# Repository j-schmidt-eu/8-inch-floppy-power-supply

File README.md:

# 8-inch floppy drive - Power supply

> The 8" floppy drive power suplly can be used to power 8-inch floppy disk drives (using a suitable cable).

## Table of Contents
- [Introduction](#Introduction)
- [Specifications](#Specifications)
- [Setup](#Setup)
- [Compatibility](#Compatibility)
- [Cables](#Cables)
- [Manufacturing](#Manufacturing)
- [FAQ](#FAQ)
- [Licensing](#Licensing)

## Introduction
Many 8-inch floppy drives use different sockets and pinouts for power delivery. They also required power lines with up to 24V DC, some may need -5V DC lines and others even need a direct 120V/230V AC connection. This is a problem, since modern ATX power supplies only supply lines up to 12V.
To solve this problem a seperate power supply is necessary that provides all necessary power lines. Different connection cables can be used to power drives with different connectors.
This project aims to provide the schematic, PCB design and firmware source code to build such a supply.
The assembly consists of two part, a regular AC-DC 24V 100W power supply and an DC-DC conversion board that generates the auxillary voltages.

## Specifications

### Assembly Specifications
- Power
  - Input voltage: 120V/230V AC
  - Maximum input current: 1.0A@120V / 0.5A@230V
  - Input Connector: 3-pin screw terminal
  - Fusing: T 2.5A@120V / T 1.6A@230V

### Board Specifications
- Power
  - Input voltage: 24V DC
  - Maximum input current: 4.2A
  - Input Connector: 4-pin screw terminal
- Maximum number of drives per adapter: 2
- Pass-through voltages:
  - 24V DC 83W
- Output voltages:
  - +5V DC 15W
  - -5V DC 2W

## Setup
The power supply can drive up to two drives (using a Y/splitter cable) and an adapter board (via AUX power socket).

### Connections
Check to manual of the drive you'd like to power for the correct pinout of the power socket.

Some drives required a direct mains AC line connection. Make sure that your drive model is compatible with your mains AC voltage!

__**Important: Connecting the wrong mains AC voltage to your drive will destoy it!**__

You can search for the right AC and DC cable in the [list of drives](#Compatibility) and/or the [list of cables](#Cables) below.

### Fusing
The power input cable should have an inline fuse holder installed. The correct fuse has to be selected depending on the voltage of the mains AC line.

_**WARNING! RISK OF ELECTRIC SHOCK! Power cable must be unplugged prior to opening the fuse holder!**_

### Start-up
Begin with all power cables disconnected. Connect the drive and the power supply with the right DC cable. (If applicable) Connect the AC adaptor cable to the drive.
Now connect the power supply and (if applicable) the AC adaptor cable to mains using a power cable.

## Compatibility
The following list shows some 8-inch floppy drive models and the respective cables that should be correct for them.

| Model | DC cable | AC cable | Tested<sup>1</sup> |
| ----- | -------- | -------- | ------ |
| Mitsubishi M2896-63 | [TE Connectivity 1-480270-0](#TE-Connectivity-1-480270-0) | - | ❓ |
| NEC FD1165 | [TE Connectivity 171822-7](#TE-Connectivity-171822-7) | - | ❓ |
| Shugart SA800<br>Shugart SA801 | [TE Connectivity 1-480270-0](#TE-Connectivity-1-480270-0) | [TE Connectivity 1-480304-0](#TE-Connectivity-1-480304-0) | ❓ |
| Shugart SA810<br>Shugart SA860 | [TE Connectivity 1-480763-0](#TE-Connectivity-1-480763-0) | - | ❓ |
| Shugart SA850<br>Shugart SA851 | [TE Connectivity 1-480270-0](#TE-Connectivity-1-480270-0) | [TE Connectivity 1-480700-0](#TE-Connectivity-1-480700-0) | ❓ |
| Tandon TM848-1E<br>Tandon TM848-2E | [TE Connectivity 1-480270-0](#TE-Connectivity-1-480270-0) | - | ❓ |
| Y-E DATA YD-180 | [TE Connectivity 1-480270-0](#TE-Connectivity-1-480270-0) | - | ✅ |

<sup>1</sup> ✅: Cable(s) have been successfully tested. ❓: Cable(s) should be correct according to the manual, but haven't been tested yet.<br>

## Cables
The cable drawings were designed using [Microsoft Visio](https://en.wikipedia.org/wiki/Microsoft_Visio). The Visio files are located in the [Cables](Cables) sub-folders.

### DC cables
#### TE Connectivity 1-480270-0
[PDF](Cables/Floppy%20DC/TE%20Connectivity%201-480270-0.pdf)<br>
[Sample image](Cables/Floppy%20DC/TE%20Connectivity%201-480270-0.jpg)

#### TE Connectivity 1-480763-0
[PDF](Cables/Floppy%20DC/TE%20Connectivity%201-480763-0.pdf)<br>
[Sample image](Cables/Floppy%20DC/TE%20Connectivity%201-480763-0.jpg)

#### TE Connectivity 171822-7
[PDF](Cables/Floppy%20DC/TE%20Connectivity%20171822-7.pdf)<br>
[Sample image](Cables/Floppy%20DC/TE%20Connectivity%20171822-7.jpg)

#### Y-cable/splitter cable
[PDF](Cables/Floppy%20DC/Y-cable,%20splitter%20cable.pdf)<br>
[Sample image](Cables/Floppy%20DC/Y-cable,%20splitter%20cable.jpg)

### AC cables
#### TE Connectivity 1-480304-0
[PDF](Cables/Floppy%20AC/TE%20Connectivity%201-480304-0.pdf)<br>
[Sample image](Cables/Floppy%20AC/TE%20Connectivity%201-480304-0.jpg)

#### TE Connectivity 1-480700-0
[PDF](Cables/Floppy%20AC/TE%20Connectivity%201-480700-0.pdf)<br>
[Sample image](Cables/Floppy%20AC/TE%20Connectivity%201-480700-0.jpg)

### AUX cable
#### TE Connectivity 171822-4
[PDF](Cables/Aux%20DC/TE%20Connectivity%20171822-4.pdf)<br>
[Sample image](Cables/Aux%20DC/TE%20Connectivity%20171822-4.jpg)

## Manufacturing
The schematics and PCB were designed using [KiCad](https://kicad-pcb.org/). The KiCad project is located in the [Schematics & PCB](Schematics%20&%20PCB) folder. 

### Schematic
[PDF](Schematics%20&%20PCB/8%20Inch%20Floppy%20Power%20Supply/8%20Inch%20Floppy%20Power%20Supply.pdf)<br>
[PNG](Schematics%20&%20PCB/8%20Inch%20Floppy%20Power%20Supply/8%20Inch%20Floppy%20Power%20Supply.png)

### PCB Gerber files
[ZIP](Schematics%20&%20PCB/8%20Inch%20Floppy%20Power%20Supply/pcb.zip)

### PCB manufacturing
The board has a size of 51.5mm x 63mm, a minimum trace distance of 0.2mm and the minimal drill diameter is 0.8mm.
There are two layers and a total of 43 holes to drill. All holes, except for the two mounting holes, are plated.

If you are within the EU, you may want to consider choosing AISLER as your PCB manufacturer.

[PCB on AISLER](https://aisler.net/p/IWASNETN)

### Bill of materials
| Reference | Component | Housing /<br>Footprint | Type | Quantity |
| --------- | --------- | ---------------------- | ---- | -------- |
| C3 | Electrolytic Capacitor 2200 µF 35V | Radial D16.0mm P7.50mm | Yageo SY035M2200B7F-1632<sup>2</sup> | 1 |
| C5 | Electrolytic Capacitor 470µF 6.3V | Radial D8.0mm P3.50mm | Yageo SY006M0470B3F-0811<sup>2</sup> | 1 |
| C7 | Electrolytic Capacitor 220µF 6.3V | Radial D8.0mm P3.50mm | Yageo SY006M0220BZF-0611<sup>2</sup> | 1 |
| C4 | Ceramic Capacitor 1µF 50V | Disc D7.5mm W4.4mm P5.00mm | Kemet C330C105M5U5TA+<sup>2</sup>  | 1 |
| C6, C8 | Ceramic Capacitor 470nF 50V | Disc D5.1mm W3.2mm P5.00mm | Kemet C322C474M5U5TA+<sup>2</sup>  | 1 |
| J1 | AUX power out socket | 1 x 2 x 2.54mm | Molex 1053131202 | 1 |
| J2 | Power in screw terminal | 1 x 2 x 9.5mm | Degson DG950-9.5-02P-14-00AH | 2 |
| J3 | Main power out socket | 2 x 4 x 3.0mm | Molex 430450800 | 1 |
| U1 | 2W 5V isolated DC-DC Converter | TRACO TMR xx | Mean Well SPAN02B-05<sup>2</sup> | 1 |
| U2 | 15W 5V isolated DC-DC Converter | TRACO TEN10 xx | Mean Well SKA15B-05<sup>2</sup> | 1 |

<sup>2</sup> Suggestion; Other types may be used. <br>

## FAQ
##### My drive is not listed in the compatibility list, will it work?
>**Check the manual of your drive to see what kind of connector and pinout is used.
Go through the available cables to see if one matches the requirments of your drive. If that is the case, the drive will very likely work.**

## Licensing
This project is licensed under the [CC BY-NC-ND 4.0 license](LICENSE).

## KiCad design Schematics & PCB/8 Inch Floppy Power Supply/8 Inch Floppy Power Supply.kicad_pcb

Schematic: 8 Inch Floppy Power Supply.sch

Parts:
C3: 2200u; CP_Radial_D16.0mm_P7.50mm
C4: 1u; C_Disc_D7.5mm_W4.4mm_P5.00mm
C5: 470u; CP_Radial_D8.0mm_P3.50mm
C6, C8: 330n; C_Disc_D5.1mm_W3.2mm_P5.00mm
C7: 220u; CP_Radial_D8.0mm_P3.50mm
J1: AUX; Molex_NanoFit_1x02x2.50mm_Angled
J2: IN; Degson DG950-9.5-04P-1Y-00AH
J3: OUT; Molex_Microfit3_Header_02x04_Angled_43045-080x
U1: SPAN02B-05; Converter_DCDC_TRACO_TMR-xxxx_THT
U2: SKE10B-05; Converter_DCDC_TRACO_TEN10-xxxx_Single_THT

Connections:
+5V_DC: C5.1, C6.1, J1.2, J3.5, U2.3
+5V_GND: C5.2, C6.2, J1.1, J3.1, U2.5
+24V_DC: C3.1, C4.1, J2.1, J2.2, J3.8, U1.2, U2.1
+24V_GND: C3.2, C4.2, J2.3, J3.4, U1.1, U1.3, U2.2
-5V_DC: C7.2, C8.2, J3.6, U1.7
-5V_GND: C7.1, C8.1, J3.2, U1.6
GND: J2.4, J3.3, J3.7

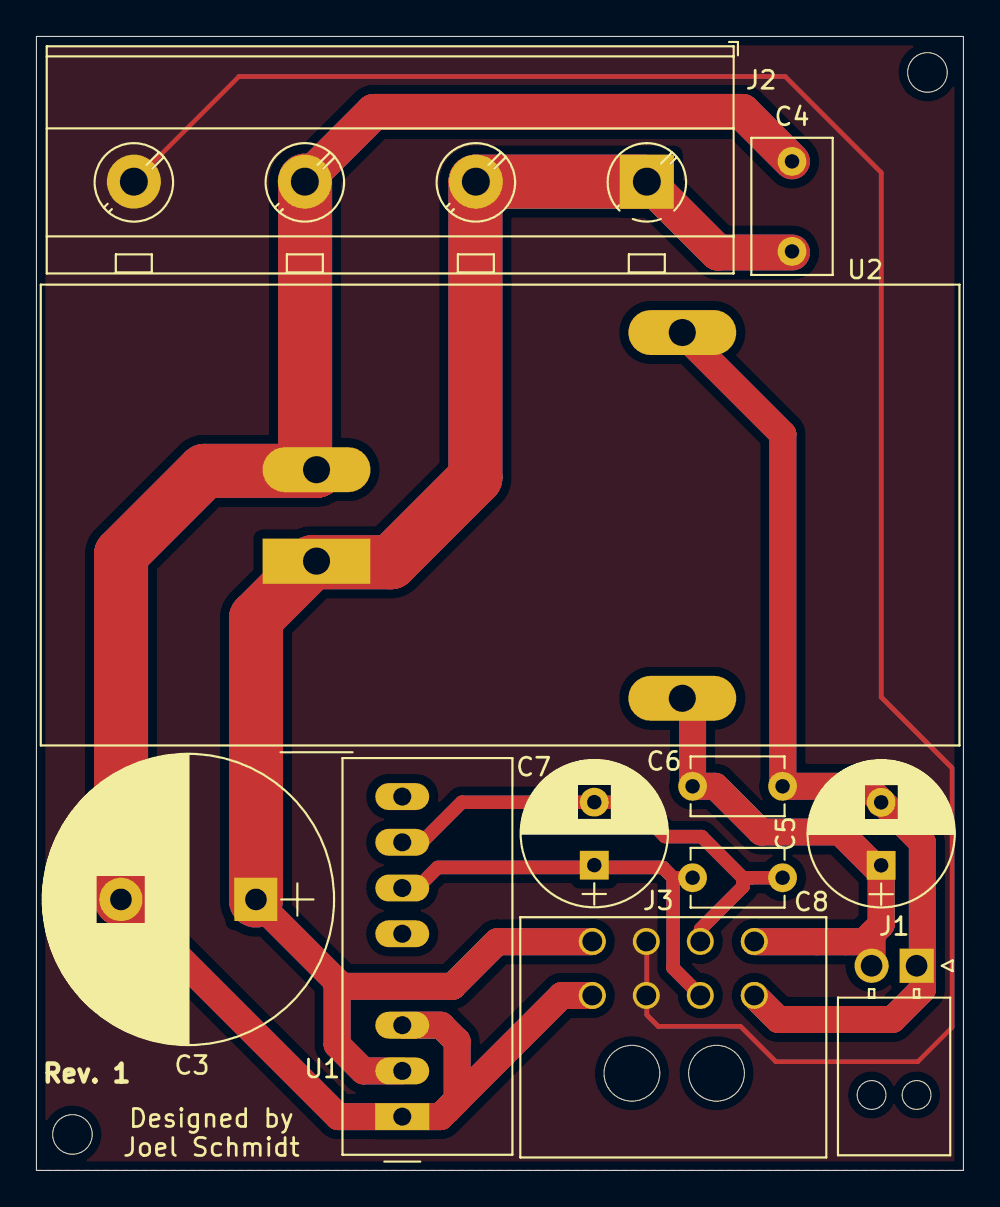
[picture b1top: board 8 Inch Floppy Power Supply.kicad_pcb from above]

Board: 2 copper layers, 51.5 x 63.0 mm, 11 parts (0 on the bottom side), 7 nets.

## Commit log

2024-02-12 PCB, cables and readme for revision 2.
